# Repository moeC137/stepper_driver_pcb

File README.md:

# stepper_driver_pcb

Video series:
https://www.youtube.com/playlist?list=PL1WGC6yQh6iIVykta8OX8R-CPlR6SFzXf

3D print files:
https://www.thingiverse.com/thing:4840651

Stepper driver board for a EDM Z-Axis in Kicad

PCB Layout

Using a Current controlled lab power supply as trigger for retraction

Using a Shunt to trigger Retraction

Shunt + hf Pulsed Source

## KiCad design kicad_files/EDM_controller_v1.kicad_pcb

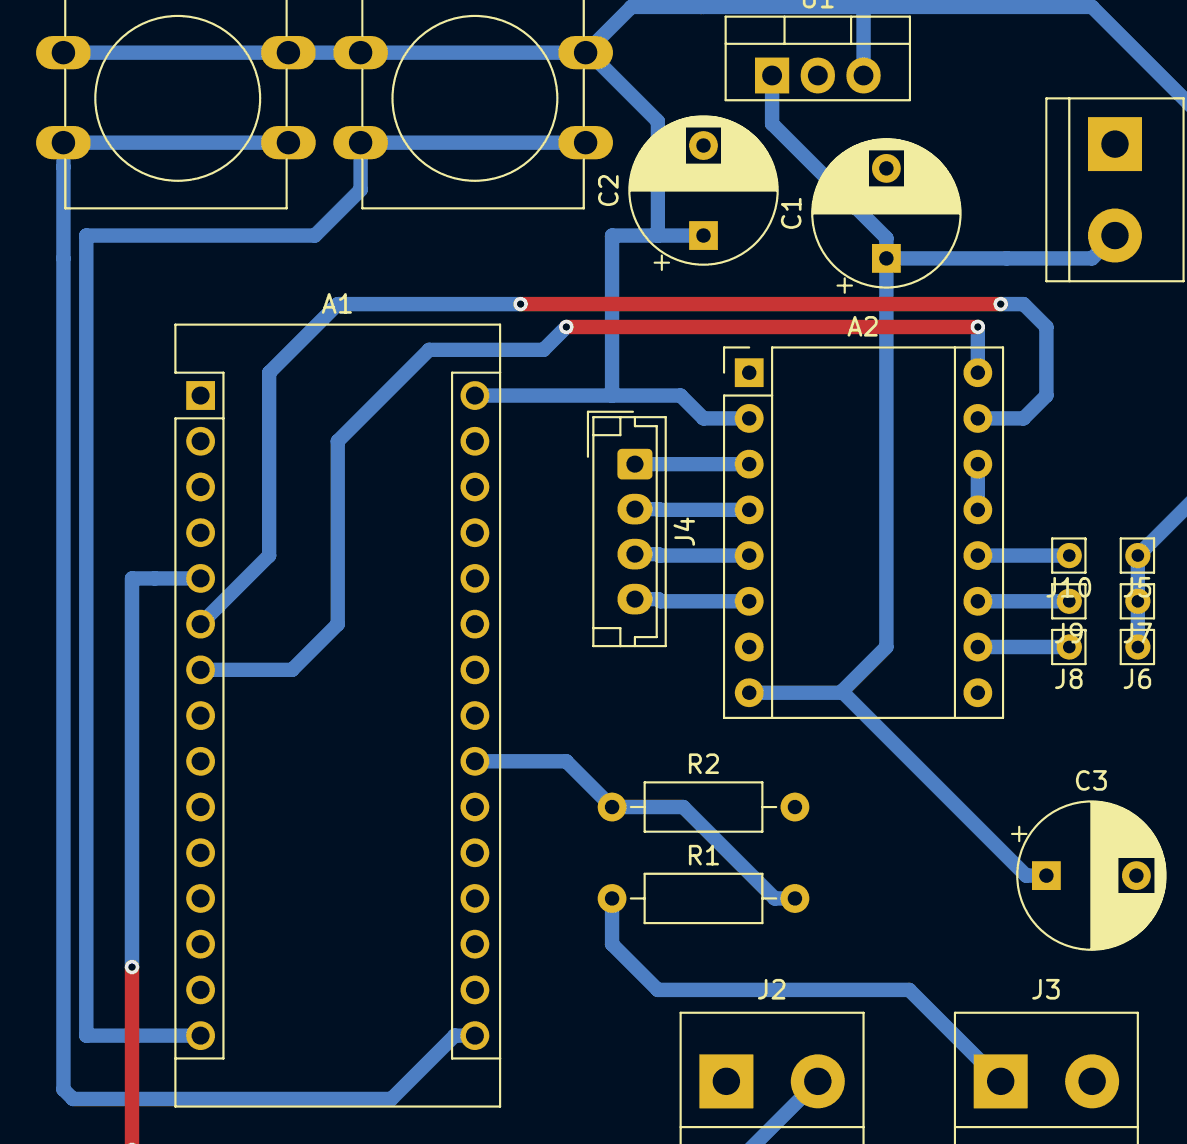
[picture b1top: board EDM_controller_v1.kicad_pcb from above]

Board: 2 copper layers, 20 parts (0 on the bottom side), 18 nets.

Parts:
A1: Arduino_Nano_v3.x; Arduino_Nano
A2: Pololu_Breakout_A4988; Pololu_Breakout-16_15.2x20.3mm
C1, C2, C3: CAP; CP_Radial_D8.0mm_P5.00mm
J1, J2, J3: Screw_Terminal_01x02; TerminalBlock_bornier-2_P5.08mm
J4: Conn_01x04; JST_EH_B4B-EH-A_1x04_P2.50mm_Vertical
J5, J6, J7, J8, J9, J10: Conn_01x01_Male; Pin_D0.7mm_L6.5mm_W1.8mm_FlatFork
R1, R2: R; R_Axial_DIN0207_L6.3mm_D2.5mm_P10.16mm_Horizontal
SW1, SW2: SW_Push_Dual; SW_PUSH-12mm
U1: L7805; TO-220-3_Vertical

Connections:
+5V: A1.30, A2.2, C2.1, J5.1, J6.1, J7.1, SW1.1, SW2.1, U1.3
+12V: A2.8, C1.1, C3.1, J1.2, U1.1
GND: A1.4, A1.29, A2.1, A2.7, C1.2, C2.2, C3.2, J1.1, J2.1, J3.2, R2.2, U1.2
unnamed: A1.5, J2.2
unnamed: A1.6, A2.15
unnamed: A1.7, A2.16
unnamed: A1.15, SW1.2
unnamed: A1.16, SW2.2
unnamed: A1.22, R1.2, R2.1
unnamed: A2.3, J4.1
unnamed: A2.4, J4.2
unnamed: A2.5, J4.3
unnamed: A2.6, J4.4
unnamed: A2.10, J8.1
unnamed: A2.11, J9.1
unnamed: A2.12, J10.1
unnamed: A2.13, A2.14
unnamed: J3.1, R1.1

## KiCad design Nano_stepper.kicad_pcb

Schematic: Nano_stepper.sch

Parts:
A1: Pololu_Breakout_A4988; Pololu_Breakout-16_15.2x20.3mm
A2: Arduino_Nano_v3.x; Arduino_Nano
C1: C_Polarized_Small; CP_Radial_D13.0mm_P7.50mm
J1: Conn_01x04_Male; JST_EH_B4B-EH-A_1x04_P2.50mm_Vertical

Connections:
+12V: A1.8 (VMOT), C1.1
GND: A1.1 (GND), A1.7 (GND), A2.4 (GND), A2.29 (GND), C1.2
unnamed: A1.2 (VDD), A2.27 (+5V)
unnamed: A1.3 (1B), J1.1
unnamed: A1.4 (1A), J1.2
unnamed: A1.5 (2A), J1.3
unnamed: A1.6 (2B), J1.4
unnamed: A1.13 (~RESET), A1.14 (~SLEEP)
unnamed: A1.15 (STEP), A2.7 (D4)
unnamed: A1.16 (DIR), A2.6 (D3)

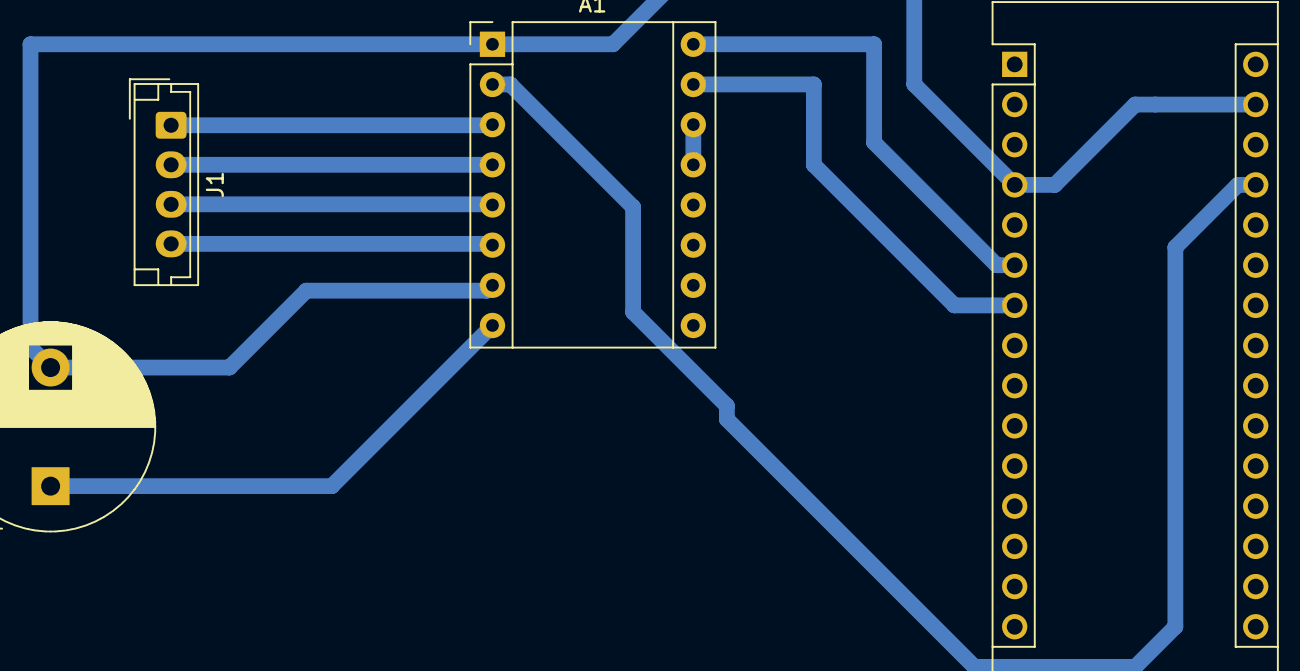
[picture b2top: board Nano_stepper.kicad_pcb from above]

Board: 2 copper layers, 4 parts (0 on the bottom side), 10 nets.

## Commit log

2021-05-09 Create kicad_files
2021-05-09 Create placeholder
